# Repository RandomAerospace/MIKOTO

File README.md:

# MIKOTO
Random weeb does weird shit lmao

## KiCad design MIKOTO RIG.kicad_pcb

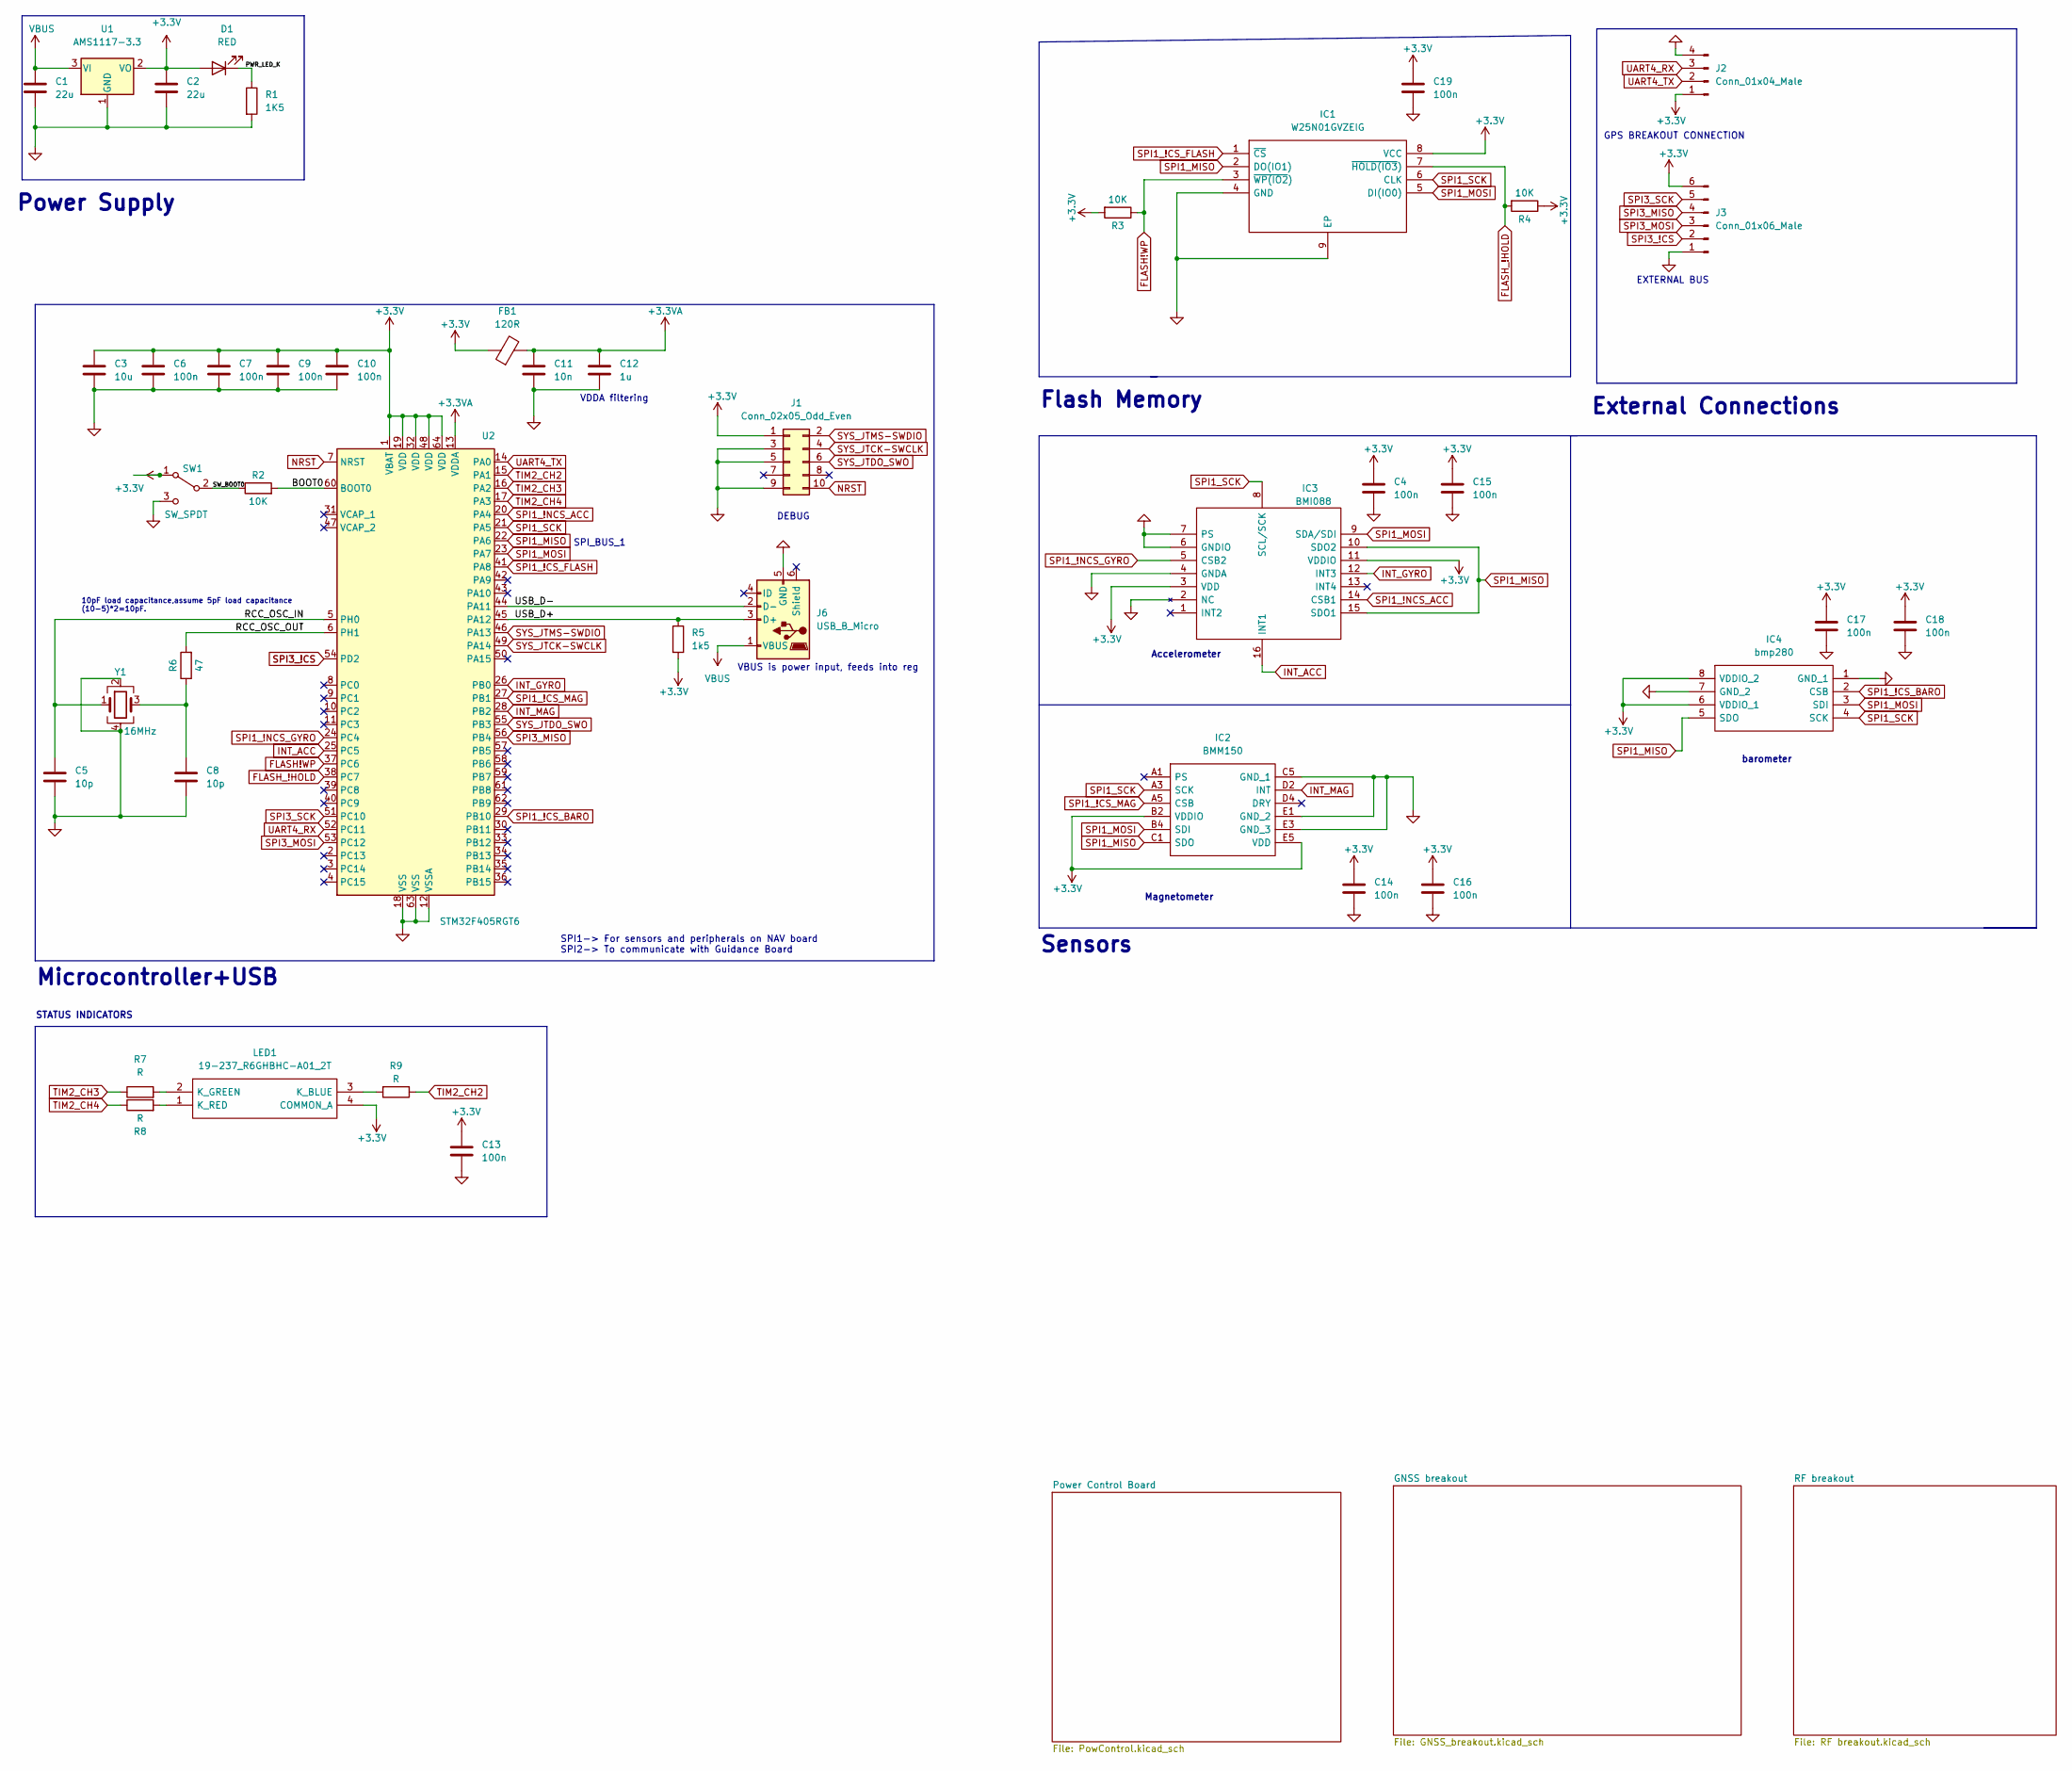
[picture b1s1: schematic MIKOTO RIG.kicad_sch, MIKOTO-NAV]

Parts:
C1, C2: 22u; C_0805_2012Metric
C3: 10u; C_0805_2012Metric
C4, C6, C7, C9, C10, C13, C14, C15, C16, C17, C18, C19: 100n; C_0805_2012Metric
C5, C8: 10p; C_0805_2012Metric
C11: 10n; C_0805_2012Metric
C12: 1u; C_0805_2012Metric
D1: RED; LED_0805_2012Metric
FB1: 120R; L_0805_2012Metric
IC1: W25N01GVZEIG; SON127P800X600X80-9N-D; Manufacturer_Part_Number W25N01GVZEIG; Mouser Part Number 454-W25N01GVZEIG
IC2: BMM150; Manufacturer_Part_Number BMM150; Mouser Part Number 262-BMM150
IC3: BMI088; Manufacturer_Part_Number BMI088; Mouser Part Number 262-BMI088
IC4: bmp280; 8-PIN-METAL-LID-LGA; Manufacturer_Part_Number bmp280; Mouser Part Number 262-BMP280
J1: Conn_02x05_Odd_Even; PinSocket_2x05_P1.27mm_Vertical_SMD
J2: Conn_01x04_Male; PinHeader_1x04_P2.54mm_Vertical
J3: Conn_01x06_Male; PinHeader_1x06_P2.54mm_Vertical
J6: USB_B_Micro; USB_Micro-B_Wuerth_629105150521
LED1: 19-237_R6GHBHC-A01_2T; 19237R6GHBHCA012T; Manufacturer_Part_Number 19-237/R6GHBHC-A01/2T; Mouser Part Number 638-19237R6GHBHCA01
R1: 1K5; R_0805_2012Metric
R2, R3, R4: 10K; R_0805_2012Metric
R5: 1k5; R_0805_2012Metric
R6: 47; R_0805_2012Metric
R7, R8, R9: R; R_0805_2012Metric
SW1: SW_SPDT; SW_SPDT_PCM12
U1: AMS1117-3.3; SOT-223-3_TabPin2
U2: STM32F405RGT6; LQFP-64_10x10mm_P0.5mm
Y1: 16MHz; Crystal_SMD_3225-4Pin_3.2x2.5mm

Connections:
+3.3VA: C11.1, C12.1, FB1.2, U2.13 (VDDA)
+3V3: C2.1, C3.1, C4.1, C6.1, C7.1, C9.1, C10.1, C13.1, C14.1, C15.1, C16.1, C17.1, C18.1, C19.1, D1.2 (A), FB1.1, IC1.8 (VCC), IC2.B2 (VDDIO), IC2.E5 (VDD), IC3.3 (VDD), IC3.11 (VDDIO), IC4.6 (VDDIO_1), IC4.8 (VDDIO_2), J1.1, J2.1, J3.6, LED1.4 (COMMON_A), R3.2, R4.1, R5.2, SW1.1 (A), U1.2 (VO), U2.1 (VBAT), U2.19 (VDD), U2.32 (VDD), U2.48 (VDD), U2.64 (VDD); also elsewhere on the board
/BOOT0: R2.2, U2.60 (BOOT0)
/PWR_LED_K: D1.1 (K), R1.1
/RCC_OSC_IN: C5.1, U2.5 (PH0), Y1.1
/RCC_OSC_OUT: R6.2, U2.6 (PH1)
/SW_BOOT0: R2.1, SW1.2 (B)
/USB_D+: J6.3 (D+), R5.1, U2.45 (PA12)
/USB_D-: J6.2 (D-), U2.44 (PA11)
FLASH!WP: IC1.3 (~WP(IO2)), R3.1, U2.37 (PC6)
FLASH_!HOLD: IC1.7 (~HOLD(IO3)), R4.2, U2.38 (PC7)
GND: C1.2, C2.2, C3.2, C4.2, C5.2, C6.2, C7.2, C8.2, C9.2, C10.2, C11.2, C12.2, C13.2, C14.2, C15.2, C16.2, C17.2, C18.2, C19.2, IC1.4 (GND), IC1.9 (EP), IC2.C5 (GND_1), IC2.E1 (GND_2), IC2.E3 (GND_3), IC3.2 (NC), IC3.4 (GNDA), IC3.6 (GNDIO), IC3.7 (PS), IC4.1 (GND_1), IC4.7 (GND_2), J1.3, J1.5, J1.9, J2.4, J3.1, J6.5 (GND), R1.2, SW1.3 (C), U1.1 (GND), U2.12 (VSSA), U2.18 (VSS), U2.63 (VSS), Y1.2, Y1.4; also elsewhere on the board
INT_ACC: IC3.16 (INT1), U2.25 (PC5)
INT_GYRO: IC3.12 (INT3), U2.26 (PB0)
INT_MAG: IC2.D2 (INT), U2.28 (PB2)
NRST: J1.10, U2.7 (NRST)
unnamed: C8.1, R6.1, Y1.3
unnamed: LED1.1 (K_RED), R8.2
unnamed: LED1.2 (K_GREEN), R7.2
unnamed: LED1.3 (K_BLUE), R9.2
SPI1_!CS_BARO: IC4.2 (CSB), U2.29 (PB10)
SPI1_!CS_FLASH: IC1.1 (~CS), U2.41 (PA8)
SPI1_!CS_MAG: IC2.A5 (CSB), U2.27 (PB1)
SPI1_!NCS_ACC: IC3.14 (CSB1), U2.20 (PA4)
SPI1_!NCS_GYRO: IC3.5 (CSB2), U2.24 (PC4)
SPI1_MISO: IC1.2 (DO(IO1)), IC2.C1 (SDO), IC3.10 (SDO2), IC3.15 (SDO1), IC4.5 (SDO), U2.22 (PA6)
SPI1_MOSI: IC1.5 (DI(IO0)), IC2.B4 (SDI), IC3.9 (SDA/SDI), IC4.3 (SDI), U2.23 (PA7)
SPI1_SCK: IC1.6 (CLK), IC2.A3 (SCK), IC3.8 (SCL/SCK), IC4.4 (SCK), U2.21 (PA5)
SPI3_!CS: J3.2, U2.54 (PD2)
SPI3_MISO: J3.4, U2.56 (PB4)
SPI3_MOSI: J3.3, U2.53 (PC12)
SPI3_SCK: J3.5, U2.51 (PC10)
SYS_JTCK-SWCLK: J1.4, U2.49 (PA14)
SYS_JTDO_SWO: J1.6, U2.55 (PB3)
SYS_JTMS-SWDIO: J1.2, U2.46 (PA13)
TIM2_CH2: R9.1, U2.15 (PA1)
TIM2_CH3: R7.1, U2.16 (PA2)
TIM2_CH4: R8.1, U2.17 (PA3)
UART4_RX: J2.3, U2.52 (PC11)
UART4_TX: J2.2, U2.14 (PA0)
VBUS: C1.1, J6.1 (VBUS), U1.3 (VI)

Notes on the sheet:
Microcontroller+USB
SPI1-> For sensors and peripherals on NAV board SPI2-> To communicate with Guidance Board
Magnetometer
STATUS INDICATORS
VDDA filtering
barometer
EXTERNAL BUS
10pF load capacitance,assume 5pF load capacitance (10-5)*2=10pF.
GPS BREAKOUT CONNECTION
SPI_BUS_1
DEBUG
Accelerometer
Sensors
Power Supply
VBUS is power input, feeds into reg
External Connections
Flash Memory

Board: 2 copper layers, 44 parts (0 on the bottom side), 41 nets, no tracks yet.

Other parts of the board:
J5: Conn_01x04_Male; PinHeader_1x04_P2.54mm_Vertical

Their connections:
+3V3: J5.1; also elsewhere on the board
GND: J5.4; also elsewhere on the board

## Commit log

2022-10-10 Added first file for PCB
    initial PCB layout and rules check done
2022-10-10 Created first README file
2022-10-10 Create LICENSE
2022-10-10 added new schematics
    MIKOTO RIG main board has been assigned footprints
2022-10-10 Add files via upload
    MIKOTO main has been updatede
2022-10-11 updated schematics
    Done adding sensors, next is to add power inlet and then start on routing
2022-10-11 Create pee
2022-10-11 Rename MIKOTO RIG.kicad_prl to Schematics/MIKOTO RIG.kicad_prl
2022-10-11 Rename GNSS_breakout.kicad_sch to Schematics/GNSS_breakout.kicad_sch
2022-10-11 Create pee1
